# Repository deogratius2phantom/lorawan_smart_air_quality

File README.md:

# lorawan_smart_air_quality
Lorawan enabled device for smart air quality monitoring

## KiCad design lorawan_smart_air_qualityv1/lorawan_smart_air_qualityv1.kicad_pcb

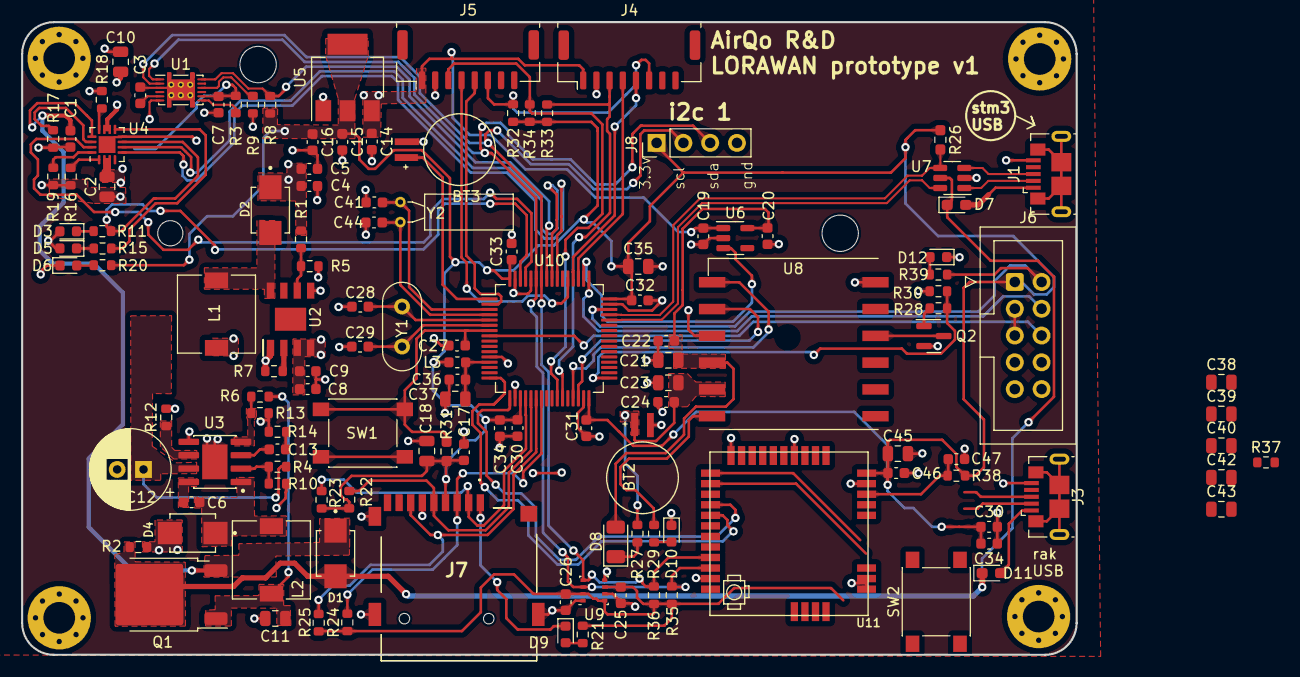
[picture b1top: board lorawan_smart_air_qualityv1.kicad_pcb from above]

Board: 2 copper layers, 100.0 x 60.0 mm, 134 parts (1 on the bottom side), 82 nets.

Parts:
BT1: Battery; BatteryHolder_Keystone_1042_1x18650
BT2, BT3: MS621FE-FL11E; BAT_MS621FE-FL11E
C1, C19, C20, C36: 1uF; C_0603_1608Metric
C2, C10, C21, C37, C45: 10uF; C_0805_2012Metric
C3: 0.47uF; C_0603_1608Metric
C4, C5, C8, C9: 2.2uF; C_0603_1608Metric
C6, C14, C15, C17, C30#2, C31, C32, C33, C34#2: 0.1uF; C_0603_1608Metric
C7: 1.0uF; C_0603_1608Metric
C11: 22UF; C_0805_2012Metric
C12: 100uF; CP_Radial_D7.5mm_P2.50mm
C13: 150pF; C_0603_1608Metric
C16: 22uF; C_0603_1608Metric
C18, C23, C35, C38, C40: 4.7uF; C_0805_2012Metric
C22, C24, C25, C26, C30, C34, C46, C47: 100nF; C_0603_1608Metric
C27: 0.1UF; C_0603_1608Metric
C28, C29, C41, C44: 12pF; C_0603_1608Metric
C39, C43: 0.1uF; C_0805_2012Metric
C42: 1uF; C_0805_2012Metric
D1: D_Schottky_Small_Filled; DIOM4336X265N
D2: D_Schottky; DIOM4336X265N
D3, D5, D10: LED_RED; LED_0603_1608Metric
D4: D; DIOM4336X265N
D6: LED_YELLOW; LED_0603_1608Metric
D7, D11: D_Schottky_Small_Filled; D_0603_1608Metric_Pad1.05x0.95mm_HandSolder
D8: D_Schottky_Small; D_1206_3216Metric
D9, D12: STATUS_LED_RED; LED_0603_1608Metric
H1, H2, H3, H4: MountingHole_Pad; MountingHole_3mm_Pad_Via
J1, J3: USB_B_Micro; USB_Micro-B_GCT_USB3076-30-A
J4, J5: Molex_CLIK-Mate_502382-0870_1x08-1MP_P1.25mm_Vertical
J6: Conn_02x05_Odd_Even; IDC-Header_2x05_P2.54mm_Vertical
J7: THD2528-11SD-GF; THD252811SDGF
J8: Conn_01x04_Pin; PinHeader_1x04_P2.54mm_Vertical
L1: 4.7UH; L_7.3x7.3_H4.5
L2: 22uH; L_7.3x7.3_H4.5
L3: 39nH; L_0603_1608Metric
Q1: PMOS; TO-252-2
Q2: BC846; SOT-23
R1: 73K; R_0603_1608Metric
R2, R4, R12, R14: 100K; R_0603_1608Metric
R3: 0.01k; R_0603_1608Metric
R5, R22, R23, R24, R25, R32, R33, R34, R35, R36, R38: 10K; R_0603_1608Metric
R6: 210K; R_0603_1608Metric
R7: 26k; R_0603_1608Metric
R8, R9, R16: 10k; R_0603_1608Metric
R10: 24.9K; R_0603_1608Metric
R11, R19, R20: 1k; R_0603_1608Metric
R13: 40.2K; R_0603_1608Metric
R15: 1.5K; R_0603_1608Metric
R17: 46.4k; R_0603_1608Metric
R18: 1K2; R_0603_1608Metric
R21: 1.8K; R_0603_1608Metric
R26: 1k5; R_0603_1608Metric_Pad0.98x0.95mm_HandSolder
R27, R29, R37, R39: 1K; R_0603_1608Metric
R28: 4.7K; R_0603_1608Metric
R30: 47K; R_0603_1608Metric
R31: 10k; R_0603_1608Metric_Pad0.98x0.95mm_HandSolder
SW1, SW2: SW_SPDT; SW_SPST_PTS645
U1: BQ27441-G1; Texas_S-PDSO-N12
U2: FP6298; SOIC127P599X175-9N
U3: MP1584EN; SOIC127P600X170-9N
U4: BQ24075RGT; VQFN-16-1EP_3x3mm_P0.5mm_EP1.6x1.6mm
U5: AMS1117-3.3; SOT-223-3_TabPin2
U6: AP2112K-3.3; SOT-23-5
U7: USBLC6-2SC6; SOT-23-6
U8: L80-R; Quectel_L80-R
U9: BME280; Bosch_LGA-8_2.5x2.5mm_P0.65mm_ClockwisePinNumbering
U10: STM32F103RCTx; LQFP-64_10x10mm_P0.5mm
U11: RAK3172
Y1: 16MH; Crystal_HC52-6mm_Vertical
Y2: 32.712K; Crystal_C38-LF_D3.0mm_L8.0mm_Horizontal

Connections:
5V_REG: C1.1, D1.1 (K), Q1.3 (S), U4.13 (IN)
+1V8: C3.1, U1.5 (V_{DD})
+3.3V: C15.1, C16.1, C17.2, C18.1, C25.1, C26.1, C30.1, C30#2.1, C31.1, C32.1, C33.1, C34.1, C34#2.1, C35.1, C38.1, C39.1, C45.1, C46.1, J6.1, J7.4 (VDD), J8.1, L3.1, R8.1, R20.1, R21.1, R22.1, R23.1, R24.1, R25.1, R26.1, R31.1, R32.1, R33.1, R34.1, R35.1, R36.1, R37.2, R38.1, U5.2 (VO), U9.2 (CSB), U9.6 (VDDIO), U9.8 (VDD), U10.19 (VDD), U10.32 (VDD), U10.48 (VDD), U10.64 (VDD), U11.24 (VDD)
+3.3VA: C36.1, C37.1, L3.2, U10.13 (VDDA)
+5V: C4.1, C5.1, C14.1, C19.1, D2.1 (K), J4.1 (VCC), J5.1 (VCC), R1.1, U5.3 (VI), U6.1 (VIN)
/BST: C6.2, U3.8 (BST)
/DCIN-(5:12V): C12.1, R4.2, U3.7 (VIN)
/EN: R4.1, R10.1, U3.2 (EN)
/FB1: R1.2, R5.1, U2.6 (FB)
/FREQ: R12.1, U3.6 (FREQ)
/ILIM: R18.1, U4.12 (ILIM)
/ISET: R19.1, U4.16 (ISET)
/LSE_IN: C41.1, U10.3 (PC14), Y2.2
/LSE_OUT: C44.1, U10.4 (PC15), Y2.1
/NRST: C27.1, R31.2, SW1.2 (B), U10.7 (NRST)
/SW: C6.1, D4.1 (K), L2.2, U3.1 (SW)
/TMR: R17.1, U4.14 (TMR)
/X: C11.1, L2.1, Q1.1 (D), R6.1
/XX: D2.2 (A), L1.2, U2.8 (LX)
BAT_STATUS: R8.2, U1.12 (GPOUT), U10.57 (PB5)
EN1: U4.6 (EN1), U10.56 (PB4)
EN2: U4.5 (EN2), U10.55 (PB3)
FB: R6.2, R13.1, U3.4 (FB)
GND: BT1.2 (-), BT2.-, BT3.-, C1.2, C2.2, C3.2, C4.2, C5.2, C7.2, C8.2, C9.2, C10.2, C11.2, C12.2, C14.2, C15.2, C16.2, C17.1, C18.2, C19.2, C20.2, C21.2, C22.2, C23.2, C24.1, C25.2, C26.2, C27.2, C28.2, C29.2, C30.2, C30#2.2, C31.2, C32.2, C33.2, C34.2, C34#2.2, C35.2, C36.2, C37.2, C38.2, C39.2, C40.2, C41.2, C42.2, C43.2, C44.2, C45.2, C46.2, C47.2, D4.2 (A), D6.1 (K), D10.1 (K), D12.1 (K), J1.5 (GND), J3.5 (GND), J4.2 (GND), J5.2 (GND), J6.3, J6.5, J7.6 (VSS), J7.MP2, J7.MP3, J7.MP4, J8.4, Q2.2 (E), R2.2, R5.2, R7.2, R9.2, R10.2, R12.2, R13.2, R14.2, R16.2, R17.2, R18.2, R19.2, R30.1, U1.3 (V_{SS}), U1.13 (PAD), U2.1 (PGND), U2.5 (GND), U3.5 (GND), U3.9 (GND), U4.8 (VSS), U4.17 (VSS), U5.1 (GND), U6.2 (GND), U7.2 (GND), U8.3 (GND), U8.12 (GND), U9.1 (GND), U9.5 (SDO), U9.7 (GND), U10.12 (VSSA), U10.18 (VSS), U10.31 (VSS), U10.47 (VSS), U10.60 (BOOT0), U10.63 (VSS), U11.11 (GND), U11.17 (GND), U11.18 (GND), U11.23 (GND), U11.28 (GND), U11.34 (GND)
GPS_3.3V: C20.1, C21.1, C22.1, D8.2 (A), U6.5 (VOUT), U8.4 (VCC)
GPS_EN: U6.3 (EN), U10.50 (PA15)
GPS_IPPS: R29.1, U8.6 (1PPS)
GPS_RESET: Q2.3 (C), U8.10 (~RESET)
GPS_RESET_PIN: R28.1, R30.2, U10.33 (PB12)
GPS_VBCKP: BT2.+, C23.1, C24.2, R27.2, U8.5 (V_BCKP)
MISO: J7.7 (DAT0), R25.2, U10.22 (PA6)
MOSI: J7.3 (CMD), R24.2, U10.23 (PA7)
NSS: J7.2 (CD/DAT3), R23.2, U10.20 (PA4)
unnamed: C13.2, R14.1
unnamed: D3.1 (K), R11.1
unnamed: D5.1 (K), R15.2
unnamed: D6.2 (A), R20.2
unnamed: D7.2 (A), J1.1 (VBUS)
unnamed: D8.1 (K), R27.1
unnamed: D9.2 (A), R21.2
unnamed: D10.2 (A), R29.2
unnamed: D11.2 (A), J3.1 (VBUS)
unnamed: D12.2 (A), R39.2
unnamed: Q2.1 (B), R28.2
unnamed: R9.1, U1.10 (BIN)
unnamed: R3.1, U1.7 (SRN)
unnamed: R7.1, U2.2 (OC)
unnamed: C13.1, U3.3 (COMP)
unnamed: R15.1, U4.9 (~CHG)
unnamed: C28.1, U10.5 (PD0), Y1.1
unnamed: C29.1, U10.6 (PD1), Y1.2
PGOOD: R11.2, U4.7 (~PGOOD), U10.62 (PB9)
PM_SENSOR1_SET: J4.3 (SET), R33.2, U10.27 (PB1)
PM_SENSOR2_SET: J5.3 (SET), R34.2, U10.26 (PB0)
PM_SENSOR_RESET: J4.6 (RESET), J5.6 (RESET), R32.2
RAK11720_RST: C47.1, R38.2, U11.22 (RST)
RAK11720_UART0_RX: U10.16 (PA2), U11.5 (GP40/UART0_RX)
RAK11720_UART0_TX: U10.17 (PA3), U11.4 (GP39/UART0_TX)
SCK: J7.5 (CLX), R22.2, U10.21 (PA5)
SCL: J8.2, R36.2, U1.2 (SCL), U9.4 (SCK), U10.58 (PB6), U11.9 (GP27/I2C2_SCL)
SDA: J8.3, R35.2, U1.1 (SDA), U9.3 (SDI), U10.59 (PB7), U11.10 (GP25/I2C2_SDA)
SD_DET: D9.1 (K), J7.1 (DAT2)
SWDCLK_STM32: J6.4, U10.49 (PA14)
SWDIO_STM32: J6.2, R39.1, U10.46 (PA13)
SWO_RAK: SW2.2 (B), U11.21 (SWO)
SWO_STM32: J6.6, U10.8 (PC0)
SYSOFF: U4.15 (SYSOFF), U10.61 (PB8)
TS: R16.1, U4.1 (TS)
UART4_RX: J4.5 (TX), U10.52 (PC11)
UART4_TX: J4.4 (RX), U10.51 (PC10)
UART5_RX: J5.5 (TX), U10.2 (PC13)
UART5_TX: J5.4 (RX), U10.53 (PC12)
USART3_RX: U8.2 (TXD1), U10.30 (PB11)
USART3_TX: U8.1 (RXD1), U10.29 (PB10)
USB_CONN_D+: J1.3 (D+), U7.3 (I/O2)
USB_CONN_D-: J1.2 (D-), U7.1 (I/O1)
USB_D+: R26.2, U7.4 (I/O2), U10.45 (PA12)
USB_D-: U7.6 (I/O1), U10.44 (PA11)
VBAT: BT1.1 (+), C2.1, C7.1, R3.2, U1.6 (BAT), U1.8 (SRP), U4.2 (BAT), U4.3 (BAT)
VIN: C8.1, C9.1, C10.1, D3.2 (A), D5.2 (A), L1.1, U2.3 (VCC), U2.4 (EN), U4.10 (OUT), U4.11 (OUT)
VRTC: BT3.+, U10.1 (VBAT)
VUSB: C42.1, C43.1, D1.2 (A), D7.1 (K), D11.1 (K), Q1.2 (G), R2.1, U7.5 (VBUS)

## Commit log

2023-10-23 modefied the booard to use CP2102 USB to USART converter, more conveneient
